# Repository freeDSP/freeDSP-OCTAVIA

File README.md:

# freeDSP-OCTAVIA
8ch Output ADAU1452/1466 DSP Board with Analog/COAX/OPT/USB/Raspberry-Pi Input

Version 1.2 is the latest commit.  
version 1.0 is evaluated and it worked.  
version 0.33j board requires some workarounds.  
version 0.33j_Fixed is a fixed design of 0.33j, But I recommend you build the latest version 1.2 or 1.1  
The errata information is detailed below...  
https://github.com/freeDSP/freeDSP-OCTAVIA/wiki/Errata-and-Workarounds

----
## Features:
* ADAU1452/1466 DSP for 2 in 8 out Audio Processing
* RCA-pin Analog Input
* Coaxial S/PDIF Input
* Optical S/PDIF Input
* Optical S/PDIF Output
* Optional Amanero Combo384 USB-Audio Interface Slot
* DSD mute protection for Amanero Combo384
* Optional Raspberry-Pi 40P Slot for I2S Audio Input  
(Raspberry-pi is optional, It is not necessary if you have a USBi for DSP programming)   
* Optional Raspberry-Pi I2C Connection to DSP
* On-board power supply for Raspberry Pi with shutdown control
* Restart/Shutdown button for Raspberry-Pi
* Independent Power switch for Raspberry-Pi
* Mains Power switch linked with Raspberry-Pi
* Common mode filtered Reverse voltage protection for Burrel DC Input
* IR Remote sensor for Raspberry-Pi
* R/G/B Power Status indicator LED
* Extra I2S Inpt header for external ADC(i.e. Phono) input source
* 8-channel RCA-pin Differential or Unbalanced Audio Output
* Balanced Output header for XLR output Connection
* 4 + 1(Master) Rotary Pots for AUX-ADC
* 4 steps + 1 mute level control Rotary switched Voltage Source for Input source selection
* LED source position indicator output header 
* I2C(0x70) connected USBi Interface with Bus-switch
* 2 LED indicators controlled by MP6 and MP7
* DSP Reset button
* Optional simple Unblanced RCA-pin output implementation capability

----
## LINKS:<br />
Wiki Page<br /> 
https://github.com/freeDSP/freeDSP-OCTAVIA/wiki

Discussion Forum:<br /> 
 https://www.diyaudio.com/community/threads/freedsp-octavia.393804/

Project Web-page:(Yandex Machine Translation)<br/>
 [Yandex Machine Translation](https://translated.turbopages.org/proxy_u/ja-en.en.1f823d34-64db980e-910d74e0-74722d776562/https/cyberpithilo.web.fc2.com/audio/FreeDSP_OCTAVIA/octavia_main.html)

Project Web-page:(Google Machine Translation)<br/>
[Google Machine Translation](https://cyberpithilo-web-fc2-com.translate.goog/audio/FreeDSP_OCTAVIA/octavia_main.html?_x_tr_sl=ja&_x_tr_tl=en&_x_tr_hl=ja&_x_tr_pto=wapp)  <BR/>

Project Web-page:(Original Japanese Page)<br/>
 [https://cyberpithilo.web.fc2.com/audio/FreeDSP_OCTAVIA/octavia_main.html](https://cyberpithilo.web.fc2.com/audio/FreeDSP_OCTAVIA/octavia_main.html)

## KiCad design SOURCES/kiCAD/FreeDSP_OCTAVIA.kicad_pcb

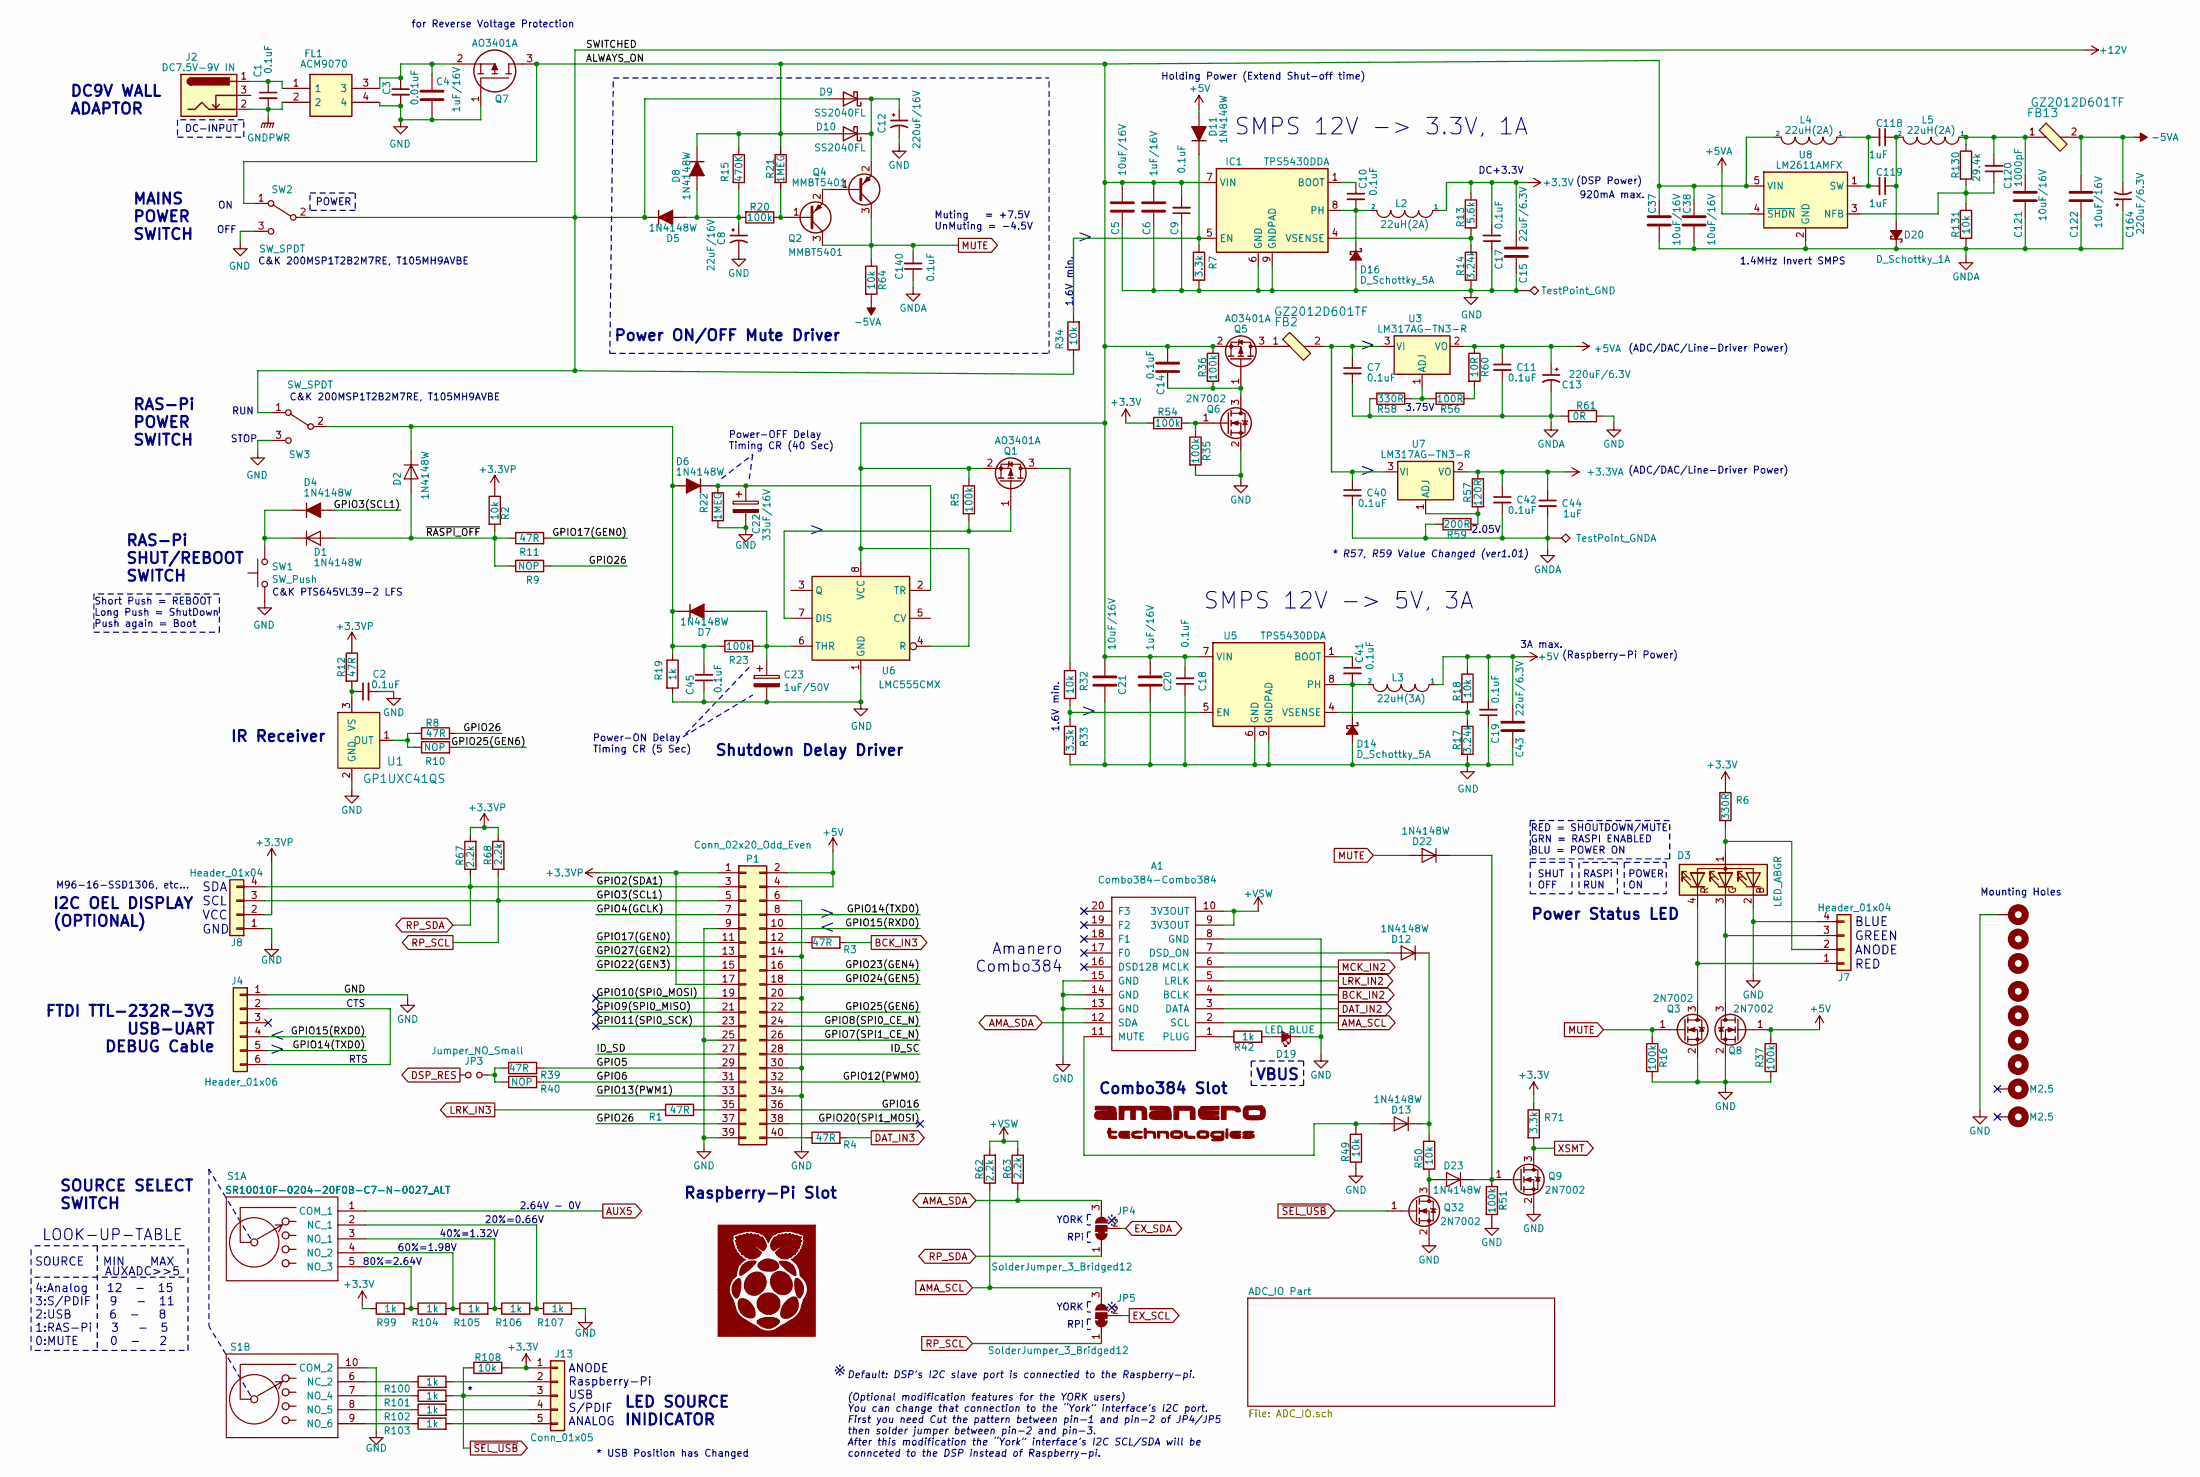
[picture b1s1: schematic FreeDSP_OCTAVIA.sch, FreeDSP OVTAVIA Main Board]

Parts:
A1: Combo384-Combo384; Combo384
C1, C2, C7, C9, C10, C11, C14, C17, C18, C19, C40, C41, C42, C45, C140: 0.1uF; C_0805_2012Metric_Pad1.18x1.45mm_HandSolder
C3: 0.01uF; C_0805_2012Metric_Pad1.18x1.45mm_HandSolder
C4, C6, C20: 1uF/16V; C_0805_2012Metric_Pad1.18x1.45mm_HandSolder
C5, C21, C37, C38, C121, C122: 10uF/16V; C_0805_2012Metric_Pad1.18x1.45mm_HandSolder
C8: 22uF/16V; CP_Radial_D5.0mm_P2.00mm
C12: 220uF/16V; CP_Radial_D7.5mm_P2.50mm
C13, C164: 220uF/6.3V; CP_Radial_D10.0mm_P2.50mm_P5.00mm
C15, C43: 22uF/6.3V; C_0805_2012Metric_Pad1.18x1.45mm_HandSolder
C22: 33uF/16V; CP_Radial_D5.0mm_P2.00mm
C23: 1uF/50V; C_0805
C44: 1uF; C_0805_2012Metric_Pad1.18x1.45mm_HandSolder
C118, C119: 1uF; C_0603_1608Metric
C120: 1000pF; C_0603_1608Metric
D1, D2, D4, D5, D6, D7, D8, D11, D12, D13, D22, D23: 1N4148W; D_SOD-123
D3: LED_ABGR; LED_0603_ABGR
D9, D10: SS2040FL; D_SOD-123
D14, D16: D_Schottky_5A; D_SMA
D19: LED_BLUE; LED_0603_1608Metric_Castellated
D20: D_Schottky_1A; D_SMA
FB2: GZ2012D601TF; L_0805_2012Metric; MPN BLM18AG601SN1D; Digi-Key_PN 490-1014-1-ND
FB13: GZ2012D601TF; 0805; MPN BLM18AG601SN1D; Digi-Key_PN 490-1014-1-ND
FL1: ACM9070; ACM9070F
IC1: TPS5430DDA; TI_SO-PowerPAD-8_ThermalVias
J2: DC7.5V-9V IN; BarrelJack_Horizontal
J4: Header_01x06; PinHeader_1x06_P2.54mm_Vertical
J7, J8: Header_01x04; PinHeader_1x04_P2.54mm_Vertical
J13: Conn_01x05; PinHeader_1x05_P2.54mm_Vertical
JP3: Jumper_NO_Small; SolderJumper-2_P1.3mm_Open_RoundedPad1.0x1.5mm
JP4, JP5: SolderJumper_3_Bridged12; SolderJumper-3_P1.3mm_Bridged12_Pad1.0x1.5mm_NumberLabels
L2, L4, L5: 22uH(2A); L_Taiyo-Yuden_NR-60xx_HandSoldering
L3: 22uH(3A); L_Taiyo-Yuden_NR-60xx_HandSoldering
MH1: M3; MountingHole_3.2mm_M3_Pad_Via
MH2, MH3, MH4, MH5, MH6, MH7: M3; MountingHole_3.2mm_M3_Pad_TopOnly
MK1, MK2: M2.5; MountingHole_2.5mm
P1: Conn_02x20_Odd_Even; PinSocket_2x20_P2.54mm_Vertical
Q1, Q5, Q7: AO3401A; SOT-23_Handsoldering; Manufacturer_Part_Number DMG3415U-7; Mouser Part Number 621-DMG3415U-7
Q2, Q4: MMBT5401; SOT-23_Handsoldering
Q3, Q6, Q8, Q9, Q32: 2N7002; SOT-23_Handsoldering
R1, R3, R4, R39: 47R; R_0603_1608Metric
R2, R18, R32, R34, R50, R64, R108: 10k; R_0805_2012Metric_Pad1.20x1.40mm_HandSolder
R5, R16, R20, R23, R35, R36, R37, R51, R54: 100k; R_0805_2012Metric_Pad1.20x1.40mm_HandSolder
R6: 330R; R_0805_2012Metric_Pad1.20x1.40mm_HandSolder
R7, R33, R71: 3.3k; R_0805_2012Metric_Pad1.20x1.40mm_HandSolder
R8, R11, R12: 47R; R_0805_2012Metric_Pad1.20x1.40mm_HandSolder
R9, R10: NOP; R_0805_2012Metric_Pad1.20x1.40mm_HandSolder
R13: 5.6k; R_0805_2012Metric_Pad1.20x1.40mm_HandSolder
R14, R17: 3.24k; R_0805_2012Metric_Pad1.20x1.40mm_HandSolder
R15: 470K; R_0805_2012Metric_Pad1.20x1.40mm_HandSolder
R19, R42, R99, R100, R101, R102, R103, R104, R105, R106, R107: 1k; R_0805_2012Metric_Pad1.20x1.40mm_HandSolder
R21, R22: 1MEG; R_0805_2012Metric_Pad1.20x1.40mm_HandSolder
R40: NOP; R_0603_1608Metric
R49, R131: 10k; R_0603_1608Metric
R56: 100R; R_0603_1608Metric
R57: 120R; R_0603_1608Metric
R58: 330R; R_0603_1608Metric
R59: 200R; R_0603_1608Metric
R60: 10R; R_0603_1608Metric
R61: 0R; R_0603_1608Metric
R62, R63, R67, R68: 2.2k; R_0603_1608Metric
R130: 29.4k; R_0603_1608Metric
S1: SR10010F-0204-20F0B-C7-N-0027_ALT; SR10010F020420F0BC7N0027; Manufacturer_Part_Number SR10010F-0204-20F0B-C7-N-0027; Mouser Part Number 105-SR10010F-24NS
SW1: SW_Push; SW_Tactile_SPST_Angled_PTS645Vx83-2LFS
SW2, SW3: SW_SPDT; 2MS1T1B4M7QES
TP1: TestPoint_GNDA; TestPoint_THTPad_2.0x2.0mm_Drill1.0mm
TP2: TestPoint_GND; TestPoint_THTPad_2.0x2.0mm_Drill1.0mm
U1: GP1UXC41QS; IR_Receiver_TSOP38238; MPN TSOP38238; Digi-Key_PN 751-1227-ND
U3, U7: LM317AG-TN3-R; TO-252-2
U5: TPS5430DDA; TI_SO-PowerPAD-8_ThermalVias
U6: LMC555CMX; SOIC-8_3.9x4.9mm_P1.27mm
U8: LM2611AMFX; SOT-23-5
Z2: LOGO; AmaneroLogo
Z3: LOGO; RasPiLogoSmall

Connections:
+3.3VA: C42.1, C44.1, R57.1, U7.2 (VO); also elsewhere on the board
+3.3VP: J8.2, P1.1, P1.17, R2.1, R12.1, R67.2, R68.1
+3V3: C15.1, C17.2, J13.1, L2.1, R6.1, R13.1, R54.1, R71.1, R99.1, R108.1; also elsewhere on the board
+5V: C19.2, C43.1, D11.2 (A), L3.1, P1.2, P1.4, Q8.1 (G), R18.1, R37.1
+5VA: C11.1, C13.1, R60.1, U3.2 (VO), U8.4 (~SHDN); also elsewhere on the board
+12V: D5.1 (K), D9.2 (A), R34.1, SW2.2 (B), SW3.1 (A)
+VSW: A1.9 (3V3OUT), A1.10 (3V3OUT), R62.2, R63.1
-5VA: C122.1, C164.2, FB13.2, R64.2; also elsewhere on the board
/ALWAYS_ON: C5.1, C6.1, C9.2, C14.1, C18.2, C20.1, C21.1, C37.1, C38.1, D8.1 (K), D10.2 (A), IC1.7 (VIN), L4.2, Q1.2 (S), Q5.2 (S), Q7.3, R5.1, R15.1, R21.1, R36.1, SW2.1 (A), U5.7 (VIN), U6.4 (R), U6.8 (VCC), U8.5 (VIN)
/GPIO4(GCLK): P1.7
/GPIO5: P1.29, R39.2
/GPIO6: P1.31, R40.2
/GPIO7(SPI1_CE_N): P1.26
/GPIO8(SPI0_CE_N): P1.24
/GPIO9(SPI0_MISO): P1.21
/GPIO10(SPI0_MOSI): P1.19
/GPIO11(SPI0_SCK): P1.23
/GPIO12(PWM0): P1.32
/GPIO13(PWM1): P1.33
/GPIO14(TXD0): J4.5, P1.8
/GPIO15(RXD0): J4.4, P1.10
/GPIO16: P1.36
/GPIO17(GEN0): P1.11, R11.2
/GPIO20(SPI1_MOSI): P1.38
/GPIO22(GEN3): P1.15
/GPIO23(GEN4): P1.16
/GPIO24(GEN5): P1.18
/GPIO25(GEN6): P1.22, R10.2
/GPIO26: P1.37, R8.1, R9.2
/GPIO27(GEN2): P1.13
/ID_SC: P1.28
/ID_SD: P1.27
/~RASPI_OFF: D1.2 (A), D2.2 (A), R2.2, R9.1, R11.1
AMA_SCL: A1.2 (SCL), JP5.3 (B), R62.1
AMA_SDA: A1.12 (SDA), JP4.3 (B), R63.2
AUX5: S1.1 (COM_1); also elsewhere on the board
BCK_IN2: A1.4 (BCLK); also elsewhere on the board
BCK_IN3: R3.2; also elsewhere on the board
DAT_IN2: A1.3 (DATA); also elsewhere on the board
DAT_IN3: R4.2; also elsewhere on the board
DSP_RES: JP3.1; also elsewhere on the board
EX_SCL: JP5.2 (C); also elsewhere on the board
EX_SDA: JP4.2 (C); also elsewhere on the board
GND: A1.8 (GND), A1.13 (GND), A1.14 (GND), A1.15 (GND), C2.2, C3.2, C4.1, C5.2, C6.2, C8.2, C9.1, C12.2, C15.2, C17.1, C18.1, C19.1, C20.2, C21.2, C22.2, C23.2, C43.2, C45.1, D3.2 (BK), D14.2 (A), D16.2 (A), D19.1 (K), FL1.4, IC1.6 (GND), IC1.9 (GNDPAD), J4.1, J7.4, J8.1, MH1.1, P1.6, P1.9, P1.14, P1.20, P1.25, P1.30, P1.34, P1.39, Q3.2 (S), Q6.2 (S), Q7.1, Q8.2 (S), Q9.2 (S), Q32.2 (S), R7.2, R14.2, R16.2, R17.2, R19.2, R22.2, R33.2, R35.2, R37.2, R49.1, R51.2, R61.1, R107.2, S1.10 (COM_2), SW1.1, SW2.3 (C), SW3.3 (C), TP2.1, U1.2 (GND), U5.6 (GND), U5.9 (GNDPAD), U6.1 (GND); also elsewhere on the board
GNDA: C7.2, C11.2, C13.2, C37.2, C38.2, C40.2, C42.2, C44.2, C121.2, C122.2, C140.1, C164.1, D20.1 (K), R58.1, R59.1, R61.2, R131.2, TP1.1, U8.2 (GND); also elsewhere on the board
GNDPWR: C1.2, FL1.2, J2.2
LRK_IN2: A1.5 (LRLK); also elsewhere on the board
LRK_IN3: R1.2; also elsewhere on the board
MCK_IN2: A1.6 (MCLK)
MUTE: C140.2, D22.2 (A), Q2.3 (C), Q3.1 (G), Q4.3 (C), R16.1, R64.1; also elsewhere on the board
unnamed: A1.1 (PLUG), R42.1
unnamed: A1.7 (DSD_ON), D12.2 (A)
unnamed: A1.11 (MUTE), D13.2 (A), R49.2
unnamed: C1.1, FL1.1, J2.1
unnamed: C2.1, R12.2, U1.3 (VS)
unnamed: C3.1, C4.2, FL1.3, Q7.2
unnamed: C8.1, D5.2 (A), D8.2 (A), R15.2, R20.2
unnamed: C10.1, IC1.1 (BOOT)
unnamed: C10.2, D16.1 (K), IC1.8 (PH), L2.2
unnamed: C12.1, D9.1 (K), D10.1 (K), Q4.2 (E)
unnamed: C14.2, Q5.1 (G), Q6.3 (D), R36.2
unnamed: C22.1, D6.1 (K), R22.1, U6.2 (TR)
unnamed: C23.1, D7.2 (A), R23.1, U6.6 (THR)
unnamed: C7.1, C40.1, FB2.2, U3.3 (VI), U7.3 (VI)
unnamed: C41.1, U5.1 (BOOT)
unnamed: C41.2, D14.1 (K), L3.2, U5.8 (PH)
unnamed: C45.2, D2.1 (K), D6.2 (A), D7.1 (K), R19.1, R23.2, SW3.2 (B)
unnamed: C118.1, C119.1, D20.2 (A), L5.2
unnamed: C118.2, C119.2, L4.1, U8.1 (SW)
unnamed: C120.1, R130.2, R131.1, U8.3 (NFB)
unnamed: C120.2, C121.1, FB13.1, L5.1, R130.1
unnamed: D1.1 (K), D4.1 (K), SW1.2
unnamed: D3.1 (A), J7.2, R6.2
unnamed: D3.3 (GK), J7.3, Q8.3 (D)
unnamed: D3.4 (RK), J7.1, Q3.3 (D)
unnamed: D11.1 (K), IC1.5 (EN), R7.1, R34.2
unnamed: D12.1 (K), D13.1 (K), R50.1
unnamed: D19.2 (A), R42.2
unnamed: D22.1 (K), D23.1 (K), Q9.1 (G), R51.1
unnamed: D23.2 (A), Q32.3 (D), R50.2
unnamed: FB2.1, Q5.3 (D)
unnamed: IC1.4 (VSENSE), R13.2, R14.1
unnamed: J4.2, J4.6
unnamed: J13.2, R100.2
unnamed: J13.4, R102.2
unnamed: J13.5, R103.2
unnamed: JP3.2, R39.1, R40.1
unnamed: P1.12, R3.1
unnamed: P1.35, R1.1
unnamed: P1.40, R4.1
unnamed: Q1.1 (G), R5.2, U6.7 (DIS)
unnamed: Q1.3 (D), R32.1
unnamed: Q2.1 (B), R20.1, R21.2
unnamed: Q2.2 (E), Q4.1 (B)
unnamed: Q6.1 (G), R35.1, R54.2
unnamed: R8.2, R10.1, U1.1 (OUT)
unnamed: R17.1, R18.2, U5.4 (VSENSE)
unnamed: R32.2, R33.1, U5.5 (EN)
unnamed: R56.1, R60.2
unnamed: R56.2, R58.2, U3.1 (ADJ)
unnamed: R57.2, R59.2, U7.1 (ADJ)
unnamed: R100.1, S1.6 (NC_2)
unnamed: R101.1, S1.7 (NO_4)
unnamed: R102.1, S1.8 (NO_5)
unnamed: R103.1, S1.9 (NO_6)
unnamed: R99.2, R104.1, S1.5 (NO_3)
unnamed: R104.2, R105.1, S1.4 (NO_2)
unnamed: R105.2, R106.1, S1.3 (NO_1)
unnamed: R106.2, R107.1, S1.2 (NC_1)
RP_SCL: D4.2 (A), J8.3, JP5.1 (A), P1.5, R68.2
RP_SDA: J8.4, JP4.1 (A), P1.3, R67.1
XSMT: Q9.3 (D), R71.2; also elsewhere on the board
~SEL_USB: J13.3, Q32.1 (G), R101.2, R108.2

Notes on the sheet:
Mounting Holes
OFF
POWER
DC+3.3V
SMPS 12V -> 3.3V, 1A
RAS-Pi POWER SWITCH
Power-OFF Delay Timing CR (40 Sec)
Power-ON Delay Timing CR (5 Sec)
(Raspberry-Pi Power)
RAS-Pi SHUT/REBOOT SWITCH
Raspberry-Pi Slot
FTDI TTL-232R-3V3 USB-UART DEBUG Cable
CTS
Power ON/OFF Mute Driver
IR Receiver
RTS
RUN
STOP
MAINS POWER SWITCH
(DSP Power)
(ADC/DAC/Line-Driver Power)
I2C OEL DISPLAY (OPTIONAL)
920mA max.
SMPS 12V -> 5V, 3A
3A max.
DC-INPUT
DC9V WALL ADAPTOR
POWER ON
RASPi RUN
Short Push = REBOOT Long Push = ShutDown Push again = Boot
SHUT OFF
1.6V min.
M96-16-SSD1306, etc…
Shutdown Delay Driver
Holding Power (Extend Shut-off time)
for Reverse Voltage Protection
Amanero Combo384
Combo384 Slot
SOURCE SELECT SWITCH
80%=2.64V

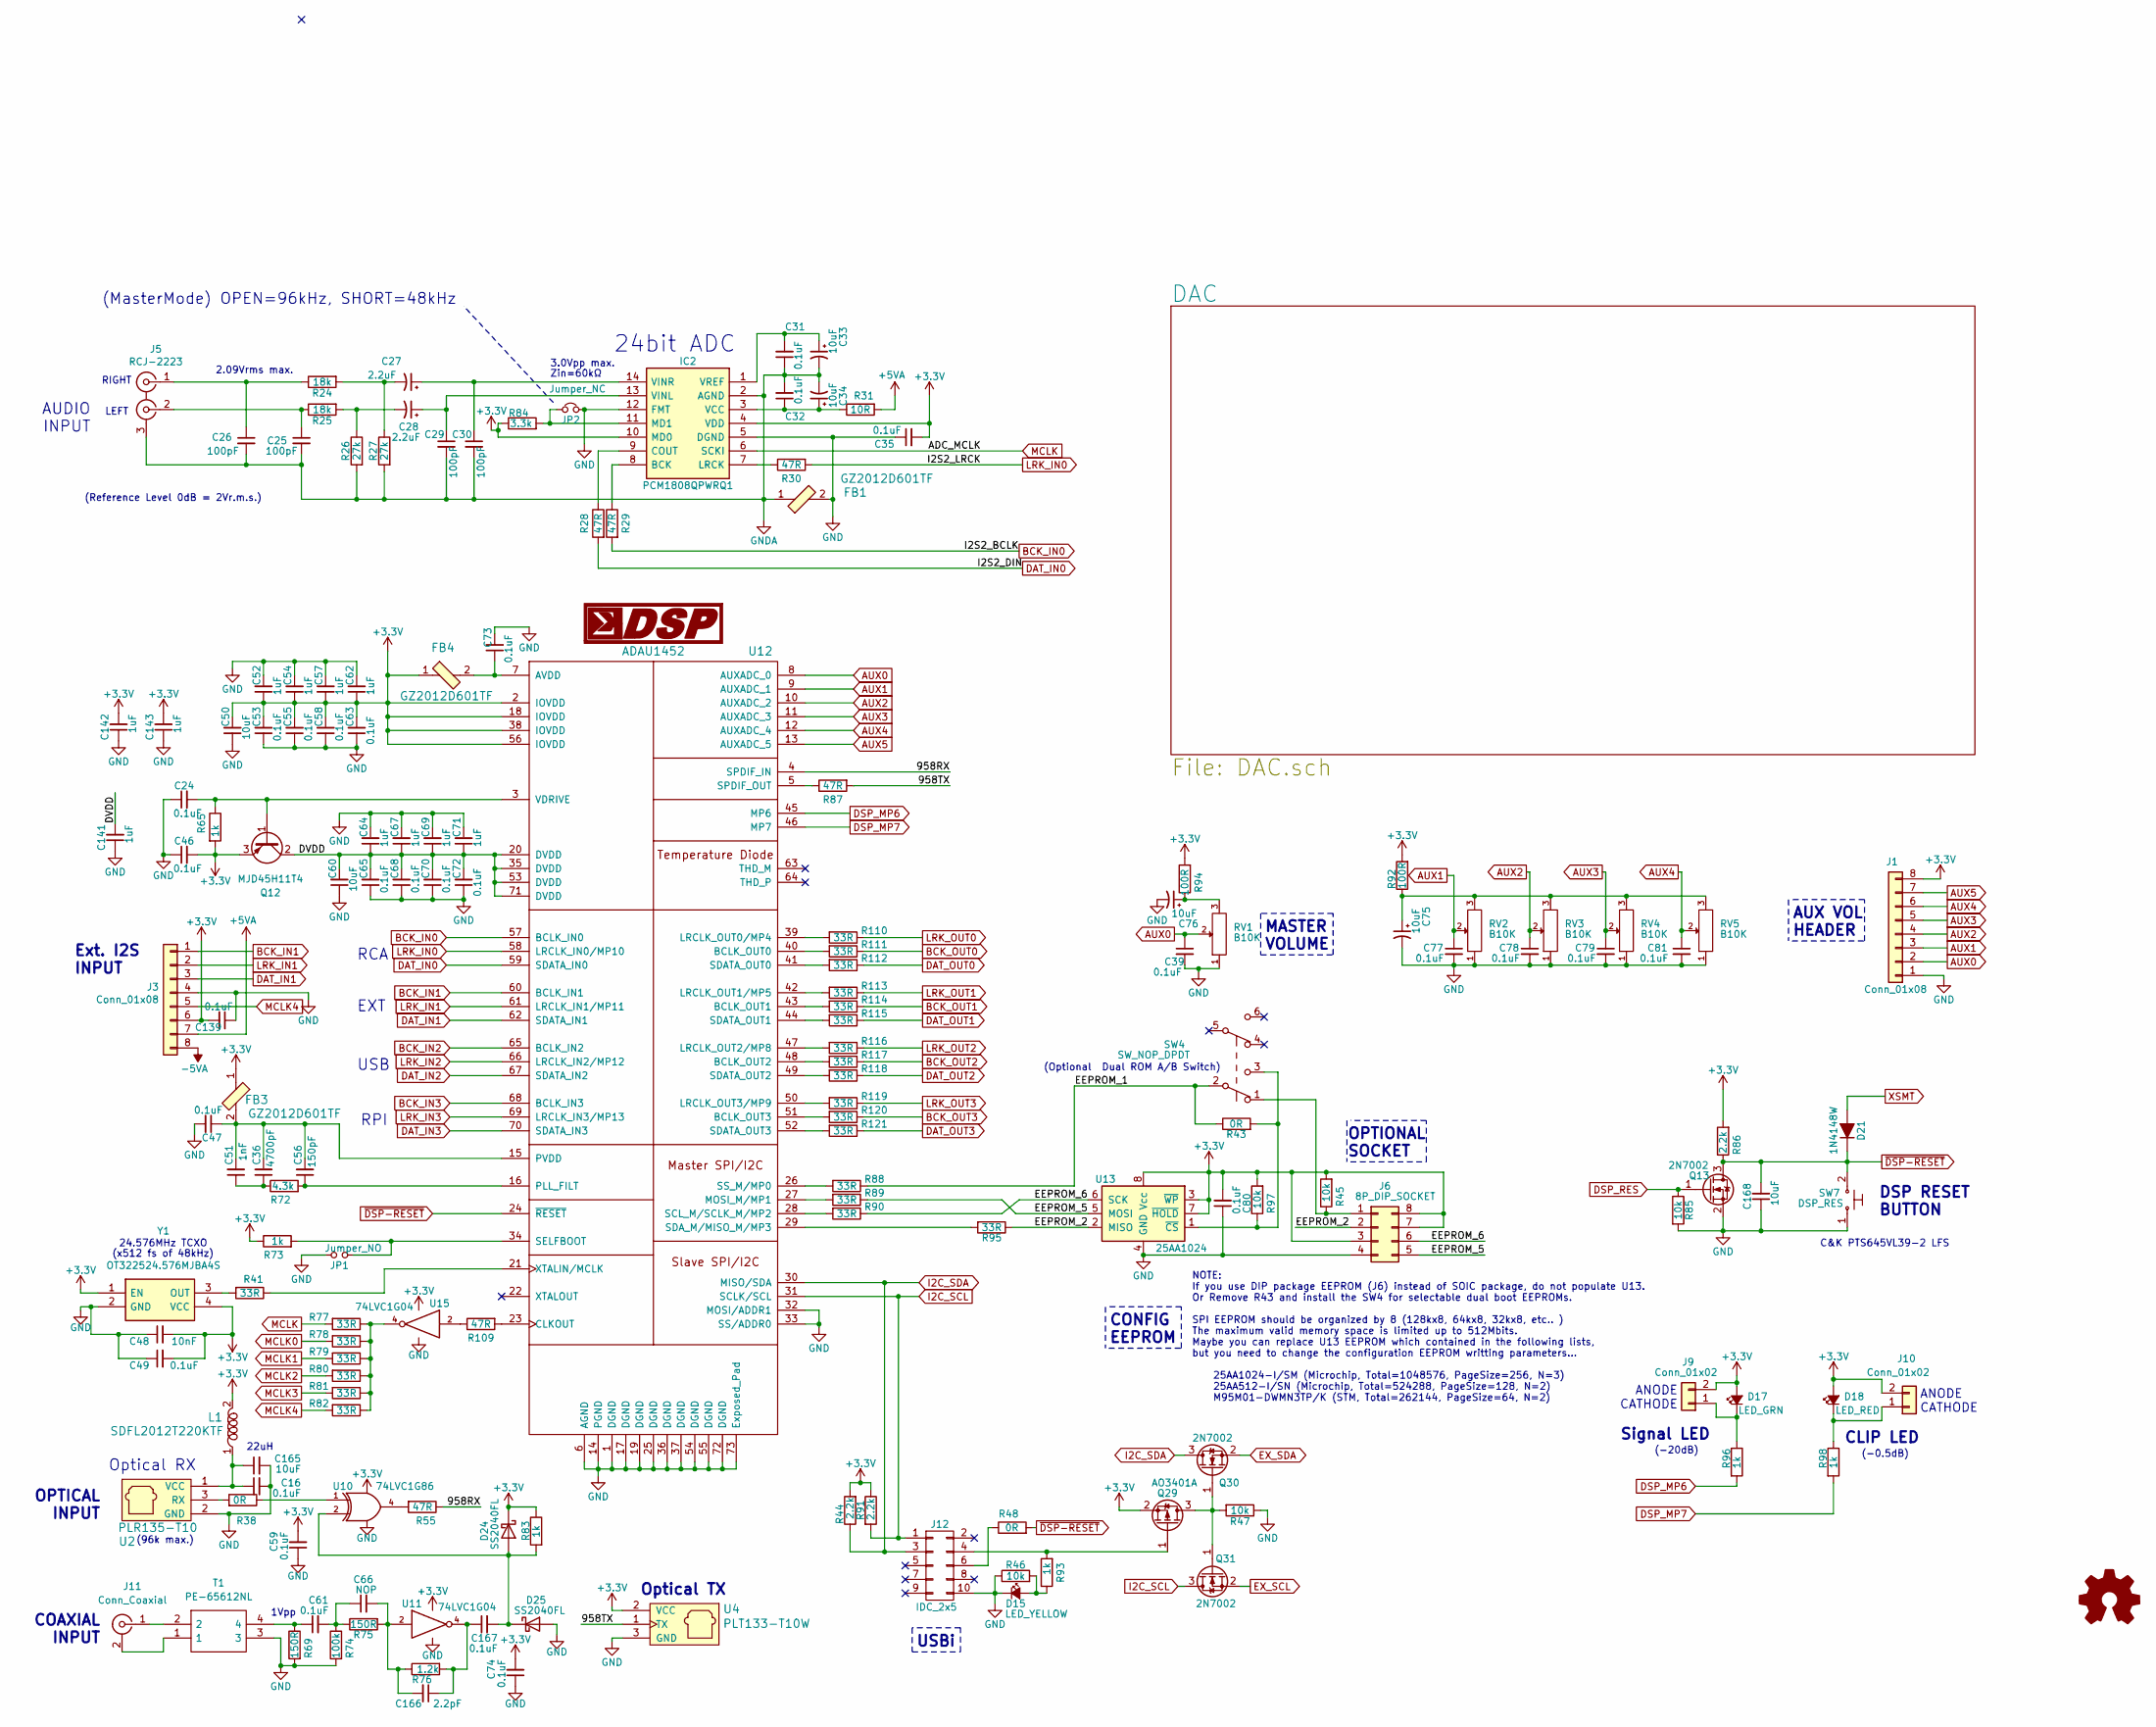
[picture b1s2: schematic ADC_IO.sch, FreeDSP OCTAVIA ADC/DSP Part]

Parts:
C16, C32, C35, C49, C53, C55, C58, C59, C61, C63, C65, C68, C70, C72, C73, C74, C80, C139, C167: 0.1uF; C_0603_1608Metric
C24, C39, C46, C47, C77, C78, C79, C81: 0.1uF; C_0805_2012Metric_Pad1.18x1.45mm_HandSolder
C25, C26, C29, C30: 100pF; C_0805_2012Metric_Pad1.18x1.45mm_HandSolder
C27, C28: 2.2uF; CP_Radial_D5.0mm_P2.00mm
C31: 0.1uF; C_0603_1608Metric_Pad1.08x0.95mm_HandSolder
C33, C60, C75, C76, C168: 10uF; C_0805_2012Metric_Pad1.18x1.45mm_HandSolder
C34, C50, C165: 10uF; C_0603_1608Metric
C36: 4700pF; C_0805_2012Metric_Pad1.18x1.45mm_HandSolder
C48: 10nF; C_0603_1608Metric
C51: 1nF; C_0805_2012Metric_Pad1.18x1.45mm_HandSolder
C52, C54, C57, C62, C64, C67, C69, C71: 1uF; C_0603_1608Metric
C56: 150pF; C_0805_2012Metric_Pad1.18x1.45mm_HandSolder
C66: NOP; C_0805_2012Metric_Pad1.18x1.45mm_HandSolder
C141, C142, C143: 1uF; C_0805_2012Metric_Pad1.18x1.45mm_HandSolder
C166: 2.2pF; C_0402_1005Metric_Pad0.74x0.62mm_HandSolder
D15: LED_YELLOW; LED_0603_1608Metric_Castellated
D17: LED_GRN; LED_0603_1608Metric_Castellated
D18: LED_RED; LED_0603_1608Metric_Castellated
D21: 1N4148W; D_SOD-123
D24, D25: SS2040FL; D_SOD-123
FB1: GZ2012D601TF; 0805; MPN BLM21PG331SN1D; Digi-Key_PN 490-5988-1-ND
FB3, FB4: GZ2012D601TF; 0805; MPN BLM18AG601SN1D; Digi-Key_PN 490-1014-1-ND
IC2: PCM1808QPWRQ1; Manufacturer_Part_Number PCM1808QPWRQ1
J1, J3: Conn_01x08; PinHeader_1x08_P2.54mm_Vertical
J5: RCJ-2223
J6: 8P_DIP_SOCKET; DIP-8_W7.62mm_Socket
J9, J10: Conn_01x02; PinHeader_1x02_P2.54mm_Vertical
J11: Conn_Coaxial; RJ-2410N
J12: IDC_2x5; IDC-Header_2x05_P2.54mm_Horizontal
JP1: Jumper_NO; SolderJumper-2_P1.3mm_Open_RoundedPad1.0x1.5mm
JP2: Jumper_NC; SolderJumper-2_P1.3mm_Bridged_RoundedPad1.0x1.5mm
L1: SDFL2012T220KTF; L_0805_2012Metric_Pad1.15x1.40mm_HandSolder; MPN 82473C; Digi-Key_PN 811-2477-1-ND
LOGO1: Logo_Open_Hardware_Small; LOGO_FREEDSP_600dpi
Q12: MJD45H11T4; TO-252-2
Q13, Q30, Q31: 2N7002; SOT-23_Handsoldering
Q29: AO3401A; SOT-23_Handsoldering; Manufacturer_Part_Number DMG3415U-7; Mouser Part Number 621-DMG3415U-7
R24, R25: 18k; R_0805_2012Metric_Pad1.20x1.40mm_HandSolder
R26, R27: 27k; R_0805_2012Metric_Pad1.20x1.40mm_HandSolder
R28, R29, R30, R55, R87, R109: 47R; R_0603_1608Metric
R31: 10R; R_0603_1608Metric
R38: 0R; R_0603_1608Metric
R41, R77, R78, R79, R80, R81, R82, R88, R89, R90, R95, R110, R111, R112, R113, R114, R115, R116, R117, R118, R119, R120, R121: 33R; R_0603_1608Metric
R43, R48: 0R; R_0805_2012Metric_Pad1.20x1.40mm_HandSolder
R44, R86, R91: 2.2k; R_0603_1608Metric
R45, R46, R47, R85, R97: 10k; R_0603_1608Metric
R65, R93, R96, R98: 1k; R_0805_2012Metric_Pad1.20x1.40mm_HandSolder
R69, R75: 150R; R_0603_1608Metric
R72: 4.3k; R_0805_2012Metric_Pad1.20x1.40mm_HandSolder
R73, R83: 1k; R_0603_1608Metric
R74: 100k; R_0603_1608Metric
R76: 1.2k; R_0603_1608Metric
R84: 3.3k; R_0603_1608Metric
R92, R94: 100R; R_0805_2012Metric_Pad1.20x1.40mm_HandSolder
RV1, RV2, RV3, RV4, RV5: B10K; RK09L12B0A31
SW4: SW_NOP_DPDT; SW_CuK_JS202011AQN_DPDT_Angled
SW7: DSP_RES; SW_Tactile_SPST_Angled_PTS645Vx83-2LFS
T1: PE-65612NL; PE65612NL; Manufacturer_Part_Number PE-65612NL; Mouser Part Number 673-PE-65612NL
U2: PLR135-T10
U4: PLT133-T10W
U10: 74LVC1G86; SOT-23-5_HandSoldering
U11, U15: 74LVC1G04; SOT-23-5_HandSoldering
U12: ADAU1452; LFCSP-72-1EP_10x10mm_P0.5mm_EP5.3x5.3mmL_HandSolder
U13: 25AA1024; SOIC-8_5.275x5.275mm_P1.27mm
Y1: OT322524.576MJBA4S; Crystal_SMD_TXC_7M-4pin_3.2x2.5mm_HandSoldering; Manufacturer_Part_Number KC7050K50.0000C1GE00
Z1: LOGO; SigmaDSP-LogoSmall

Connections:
+3V3: C35.2, C46.2, C48.2, C49.2, C50.2, C52.1, C53.2, C54.1, C55.2, C57.1, C58.2, C59.2, C62.1, C63.2, C74.2, C80.2, C139.2, C142.2, C143.2, D17.2 (A), D18.2 (A), D24.1 (K), FB3.1, FB4.1, IC2.4 (VDD), IC2.10 (MD0), J1.8, J3.6, J6.3, J6.7, J6.8, J9.2, J10.2, L1.2, Q12.3 (E), Q29.2 (S), R44.2, R45.2, R65.2, R73.1, R83.1, R84.1, R86.2, R91.1, R92.2, R94.2, R97.2, U4.2 (VCC), U10.5 (VCC), U11.5 (VCC), U12.2 (IOVDD), U12.18 (IOVDD), U12.38 (IOVDD), U12.56 (IOVDD), U13.3 (~WP), U13.7 (~HOLD), U13.8 (Vcc), U15.5 (VCC), Y1.1 (EN), Y1.4 (VCC); also elsewhere on the board
+5VA: J3.7, R31.2; also elsewhere on the board
-5VA: J3.8; also elsewhere on the board
/ADC_IO Part/958RX: R55.1, U12.4 (SPDIF_IN)
/ADC_IO Part/958TX: R87.2, U4.1 (TX)
/ADC_IO Part/DVDD: C60.2, C64.1, C65.2, C67.1, C68.2, C69.1, C70.2, C71.1, C72.2, C141.2, Q12.2 (C), U12.20 (DVDD), U12.35 (DVDD), U12.53 (DVDD), U12.71 (DVDD)
/ADC_IO Part/EEPROM_1: R43.1, R88.1, SW4.2 (B)
/ADC_IO Part/EEPROM_2: J6.2, R95.1, U13.2 (MISO)
/ADC_IO Part/EEPROM_5: J6.5, R89.1, U13.5 (MOSI)
/ADC_IO Part/EEPROM_6: J6.6, R90.1, U13.6 (SCK)
AUX0: C39.1, J1.2, RV1.2, U12.8 (AUXADC_0)
AUX1: C77.1, J1.3, RV2.2, U12.9 (AUXADC_1)
AUX2: C78.1, J1.4, RV3.2, U12.10 (AUXADC_2)
AUX3: C79.1, J1.5, RV4.2, U12.11 (AUXADC_3)
AUX4: C81.1, J1.6, RV5.2, U12.12 (AUXADC_4)
AUX5: J1.7, U12.13 (AUXADC_5); also elsewhere on the board
BCK_IN0: R29.2, U12.57 (BCLK_IN0)
BCK_IN1: J3.1, U12.60 (BCLK_IN1)
BCK_IN2: U12.65 (BCLK_IN2); also elsewhere on the board
BCK_IN3: U12.68 (BCLK_IN3); also elsewhere on the board
BCK_OUT0: R111.1; also elsewhere on the board
BCK_OUT1: R114.1; also elsewhere on the board
BCK_OUT2: R117.1; also elsewhere on the board
BCK_OUT3: R120.1; also elsewhere on the board
DAT_IN0: R28.2, U12.59 (SDATA_IN0)
DAT_IN1: J3.3, U12.62 (SDATA_IN1)
DAT_IN2: U12.67 (SDATA_IN2); also elsewhere on the board
DAT_IN3: U12.70 (SDATA_IN3); also elsewhere on the board
DAT_OUT0: R112.1; also elsewhere on the board
DAT_OUT1: R115.1; also elsewhere on the board
DAT_OUT2: R118.1; also elsewhere on the board
DAT_OUT3: R121.1; also elsewhere on the board
DSP_MP6: R96.2, U12.45 (MP6)
DSP_MP7: R98.2, U12.46 (MP7)
DSP_RES: Q13.1 (G), R85.1; also elsewhere on the board
EX_SCL: Q31.2 (S); also elsewhere on the board
EX_SDA: Q30.2 (S); also elsewhere on the board
GND: C16.2, C24.1, C35.1, C39.2, C46.1, C47.2, C48.1, C49.1, C50.1, C52.2, C53.1, C54.2, C55.1, C57.2, C58.1, C59.1, C60.1, C62.2, C63.1, C64.2, C65.1, C67.2, C68.1, C69.2, C70.1, C71.2, C72.1, C73.2, C74.1, C75.2, C76.2, C77.2, C78.2, C79.2, C80.1, C81.2, C139.1, C141.1, C142.1, C143.1, C165.2, C168.1, D15.1 (K), D25.2 (A), FB1.2, IC2.5 (DGND), IC2.12 (FMT), J1.1, J3.4, J6.4, J12.10, JP1.1, JP2.2, Q13.2 (S), R46.1, R47.1, R69.2, R74.2, R85.2, RV1.1, RV2.1, RV3.1, RV4.1, RV5.1, SW7.1, T1.3, U2.2 (GND), U4.3 (GND), U10.3 (GND), U11.3 (GND), U12.1 (DGND), U12.6 (AGND), U12.14 (PGND), U12.17 (DGND), U12.19 (DGND), U12.25 (DGND), U12.32 (MOSI/ADDR1), U12.33 (SS/ADDR0), U12.36 (DGND), U12.37 (DGND), U12.54 (DGND), U12.55 (DGND), U12.72 (DGND), U12.73 (Exposed_Pad), U13.4 (GND), U15.3 (GND), Y1.2 (GND); also elsewhere on the board
GNDA: C25.2, C26.2, C29.2, C30.2, C31.1, C32.2, C33.2, C34.2, FB1.1, IC2.2 (AGND), J5.3 (EXT), R26.2, R27.2; also elsewhere on the board
I2C_SCL: J12.1, Q31.3 (D), R91.2, U12.31 (SCLK/SCL)
I2C_SDA: J12.3, Q30.3 (D), R44.1, U12.30 (MISO/SDA)
LRK_IN0: R30.2, U12.58 (LRCLK_IN0/MP10)
LRK_IN1: J3.2, U12.61 (LRCLK_IN1/MP11)
LRK_IN2: U12.66 (LRCLK_IN2/MP12); also elsewhere on the board
LRK_IN3: U12.69 (LRCLK_IN3/MP13); also elsewhere on the board
LRK_OUT0: R110.1; also elsewhere on the board
LRK_OUT1: R113.1; also elsewhere on the board
LRK_OUT2: R116.1; also elsewhere on the board
LRK_OUT3: R119.1; also elsewhere on the board
MCLK: IC2.6 (SCKI), R77.2
MCLK0: R78.2; also elsewhere on the board
MCLK1: R79.2; also elsewhere on the board
MCLK2: R80.2; also elsewhere on the board
MCLK3: R81.2; also elsewhere on the board
MCLK4: J3.5, R82.2
unnamed: C16.1, C165.1, L1.1, U2.1 (VCC)
unnamed: C24.2, Q12.1 (B), R65.1, U12.3 (VDRIVE)
unnamed: C25.1, J5.2 (IN2), R25.1
unnamed: C26.1, J5.1 (IN1), R24.1
unnamed: C27.1, C30.1, IC2.14 (VINR)
unnamed: C27.2, R24.2, R27.1
unnamed: C28.1, C29.1, IC2.13 (VINL)
unnamed: C28.2, R25.2, R26.1
unnamed: C31.2, C33.1, IC2.1 (VREF)
unnamed: C32.1, C34.1, IC2.3 (VCC), R31.1
unnamed: C36.1, C51.1, R72.1
unnamed: C36.2, C47.1, C51.2, C56.2, FB3.2, U12.15 (PVDD)
unnamed: C56.1, R72.2, U12.16 (PLL_FILT)
unnamed: C61.1, R69.1, T1.4
unnamed: C61.2, C66.1, R74.1, R75.1
unnamed: C73.1, FB4.2, U12.7 (AVDD)
unnamed: C75.1, R92.1, RV2.3, RV3.3, RV4.3, RV5.3
unnamed: C76.1, R94.1, RV1.3
unnamed: C166.1, C167.1, R76.2, U11.4
unnamed: C66.2, C166.2, R75.2, R76.1, U11.2
unnamed: C167.2, D24.2 (A), D25.1 (K), R83.2, U10.2
unnamed: D15.2 (A), R46.2, R93.1
unnamed: D17.1 (K), J9.1, R96.1
unnamed: D18.1 (K), J10.1, R98.1
unnamed: IC2.7 (LRCK), R30.1
unnamed: IC2.8 (BCK), R29.1
unnamed: IC2.9 (COUT), R28.1
unnamed: IC2.11 (MD1), JP2.1, R84.2
unnamed: J6.1, R45.1, SW4.1 (A)
unnamed: J11.1 (In), T1.2
unnamed: J11.2 (Ext), T1.1
unnamed: J12.4, Q29.1 (G), R93.2
unnamed: J12.6, R48.1
unnamed: JP1.2, R73.2, U12.34 (SELFBOOT)
unnamed: Q29.3 (D), Q30.1 (G), Q31.1 (G), R47.2
unnamed: R38.1, U10.1
unnamed: R38.2, U2.3 (RX)
unnamed: R41.1, U12.21 (XTALIN/MCLK)
unnamed: R41.2, Y1.3 (OUT)
unnamed: R43.2, R97.1, SW4.3 (C), U13.1 (~CS)
unnamed: R55.2, U10.4
unnamed: R77.1, R78.1, R79.1, R80.1, R81.1, R82.1, U15.4
unnamed: R87.1, U12.5 (SPDIF_OUT)
unnamed: R88.2, U12.26 (SS_M/MP0)
unnamed: R89.2, U12.27 (MOSI_M/MP1)
unnamed: R90.2, U12.28 (SCL_M/SCLK_M/MP2)
unnamed: R95.2, U12.29 (SDA_M/MISO_M/MP3)
unnamed: R109.1, U15.2
unnamed: R109.2, U12.23 (CLKOUT)
unnamed: R110.2, U12.39 (LRCLK_OUT0/MP4)
unnamed: R111.2, U12.40 (BCLK_OUT0)
unnamed: R112.2, U12.41 (SDATA_OUT0)
unnamed: R113.2, U12.42 (LRCLK_OUT1/MP5)
unnamed: R114.2, U12.43 (BCLK_OUT1)
unnamed: R115.2, U12.44 (SDATA_OUT1)
unnamed: R116.2, U12.47 (LRCLK_OUT2/MP8)
unnamed: R117.2, U12.48 (BCLK_OUT2)
unnamed: R118.2, U12.49 (SDATA_OUT2)
unnamed: R119.2, U12.50 (LRCLK_OUT3/MP9)
unnamed: R120.2, U12.51 (BCLK_OUT3)
unnamed: R121.2, U12.52 (SDATA_OUT3)
XSMT: D21.2 (A); also elsewhere on the board
~DSP-RESET: C168.2, D21.1 (K), Q13.3 (D), R48.2, R86.1, SW7.2, U12.24 (~RESET)

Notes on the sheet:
(MasterMode) OPEN=96kHz, SHORT=48kHz
AUDIO INPUT
24bit ADC
(Reference Level 0dB = 2Vr.m.s.)
3.0Vpp max.
Zin=60kΩ
2.09Vrms max.
Optical TX
(96k max.)
OPTICAL INPUT
22uH
Optical RX
Ext. I2S INPUT
Signal LED
CLIP LED
(-20dB)
(-0.5dB)
DSP RESET BUTTON
USBi
MASTER VOLUME
24.576MHz TCXO
AUX VOL HEADER
CONFIG EEPROM
OPTIONAL SOCKET
USB
RPI
EXT
RCA
NOTE: If you use DIP package EEPROM (J6) instead of SOIC package, do not populate U13. Or Remove R43 and install the SW4 for selectable dual boot EEPROMs. SPI EEPROM should be organized by 8 (128kx8, 64kx8, 32kx8, etc.. ) The maximum valid memory space is limited up to 512Mbits. Maybe you can repla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
ANODE CATHODE
RIGHT
LEFT
COAXIAL INPUT
1Vpp
(x512 fs of 48kHz)
(Optional Dual ROM A/B Switch)
C&K PTS645VL39-2 LFS
